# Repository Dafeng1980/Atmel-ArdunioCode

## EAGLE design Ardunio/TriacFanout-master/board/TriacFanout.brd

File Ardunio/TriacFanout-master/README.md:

Triac Fanout board for daisy-chainable 8x triac (lightbulb) outputs and Arduino library. So far tested for 8 channels.

[Video](http://instagram.com/p/sIGZ_VrQKr/?modal=true)

Written by Sean McIntyre.
MIT license, all text above must be included in any redistribution

Place the TriacFanout library folder in your <arduinosketchfolder>/libraries/ folder. You may need to create the libraries subfolder if its your first library. Restart the IDE

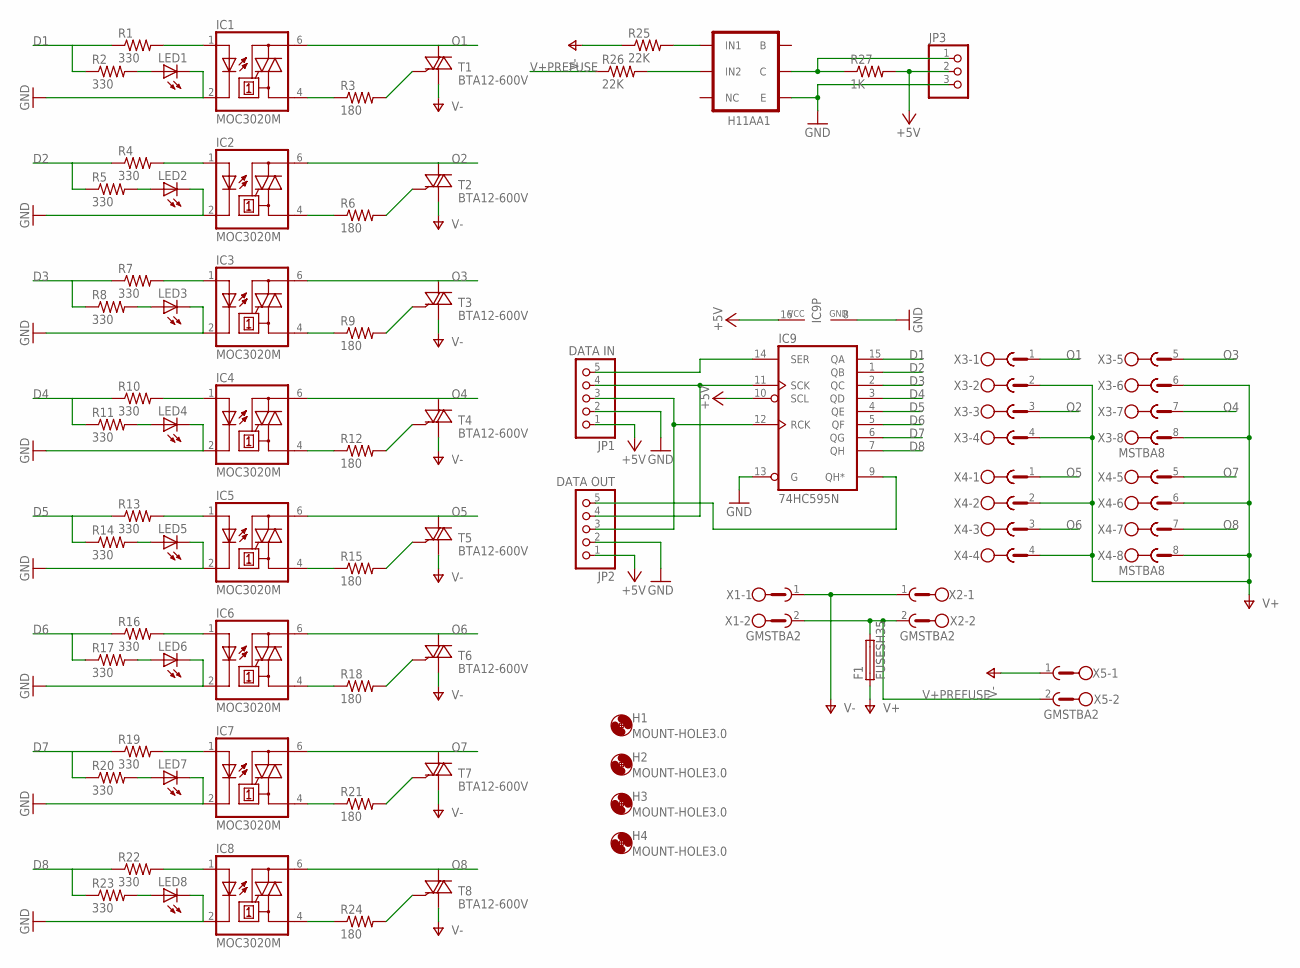
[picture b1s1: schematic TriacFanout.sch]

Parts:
F1: FUSESH35; SH25
H1, H2, H3, H4: MOUNT-HOLE3.0; 3,0
IC1, IC2, IC3, IC4, IC5, IC6, IC7, IC8: MOC3020M; DIL06
IC9: 74HC595N; DIL16
JP1: DATA IN; 1X05
JP2: DATA OUT; 1X05
JP3: PINHD-1X3; 1X03
LED1, LED2, LED3, LED4, LED5, LED6, LED7, LED8: LED5MM
R1, R2, R4, R5, R7, R8, R10, R11, R13, R14, R16, R17, R19, R20, R22, R23: 330; 0207/10
R3, R6, R9, R12, R15, R18, R21, R24: 180; 0207/10
R25, R26: 22K; 0411/12
R27: 1K; 0207/10
T1, T2, T3, T4, T5, T6, T7, T8: BTA12-600V; TO220V
U$1: H11AA1; DIL06
X1, X2, X5: GMSTBA2
X3, X4: MSTBA8

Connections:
+5V: IC9.10 (SCL), IC9.16 (VCC), JP1.1, JP2.1, JP3.2, R27.2
CLOCK: IC9.11 (SCK), JP1.4, JP2.4
D1: IC9.15 (QA), R1.1, R2.1
D2: IC9.1 (QB), R4.1, R5.1
D3: IC9.2 (QC), R7.1, R8.1
D4: IC9.3 (QD), R10.1, R11.1
D5: IC9.4 (QE), R13.1, R14.1
D6: IC9.5 (QF), R16.1, R17.1
D7: IC9.6 (QG), R19.1, R20.1
D8: IC9.7 (QH), R22.1, R23.1
DATA: IC9.14 (SER), JP1.5
GND: IC1.2 (C), IC2.2 (C), IC3.2 (C), IC4.2 (C), IC5.2 (C), IC6.2 (C), IC7.2 (C), IC8.2 (C), IC9.8 (GND), IC9.13 (G), JP1.2, JP2.2, JP3.3, LED1.K (C), LED2.K (C), LED3.K (C), LED4.K (C), LED5.K (C), LED6.K (C), LED7.K (C), LED8.K (C), U$1.4 (E)
LATCH: IC9.12 (RCK), JP1.3, JP2.3
unnamed: IC2.1 (A), R4.2
unnamed: LED2.A, R5.2
unnamed: IC2.4 (A1), R6.1
unnamed: R6.2, T2.3 (G)
unnamed: IC3.1 (A), R7.2
unnamed: LED3.A, R8.2
unnamed: IC3.4 (A1), R9.1
unnamed: R9.2, T3.3 (G)
unnamed: IC1.4 (A1), R3.1
unnamed: IC1.1 (A), R1.2
unnamed: R3.2, T1.3 (G)
unnamed: LED1.A, R2.2
unnamed: IC4.1 (A), R10.2
unnamed: LED4.A, R11.2
unnamed: IC4.4 (A1), R12.1
unnamed: R12.2, T4.3 (G)
unnamed: IC5.1 (A), R13.2
unnamed: LED5.A, R14.2
unnamed: IC5.4 (A1), R15.1
unnamed: R15.2, T5.3 (G)
unnamed: IC6.1 (A), R16.2
unnamed: LED6.A, R17.2
unnamed: IC6.4 (A1), R18.1
unnamed: R18.2, T6.3 (G)
unnamed: IC7.1 (A), R19.2
unnamed: LED7.A, R20.2
unnamed: IC7.4 (A1), R21.1
unnamed: R21.2, T7.3 (G)
unnamed: IC8.1 (A), R22.2
unnamed: LED8.A, R23.2
unnamed: IC8.4 (A1), R24.1
unnamed: R24.2, T8.3 (G)
unnamed: R25.2, U$1.1 (IN1)
unnamed: R26.2, U$1.2 (IN2)
O1: IC1.6 (A2), T1.2 (A2), X3.1
O2: IC2.6 (A2), T2.2 (A2), X3.3
O3: IC3.6 (A2), T3.2 (A2), X3.5
O4: IC4.6 (A2), T4.2 (A2), X3.7
O5: IC5.6 (A2), T5.2 (A2), X4.1
O6: IC6.6 (A2), T6.2 (A2), X4.3
O7: IC7.6 (A2), T7.2 (A2), X4.5
O8: IC8.6 (A2), T8.2 (A2), X4.7
OVERFLOW: IC9.9 (QH*), JP2.5
V+: F1.1, X3.2, X3.4, X3.6, X3.8, X4.2, X4.4, X4.6, X4.8
V+PREFUSE: F1.2, R26.1, X1.2, X2.2, X5.2
V-: R25.1, T1.1 (A1), T2.1 (A1), T3.1 (A1), T4.1 (A1), T5.1 (A1), T6.1 (A1), T7.1 (A1), T8.1 (A1), X1.1, X2.1, X5.1
ZEROCROSS: JP3.1, R27.1, U$1.5 (C)

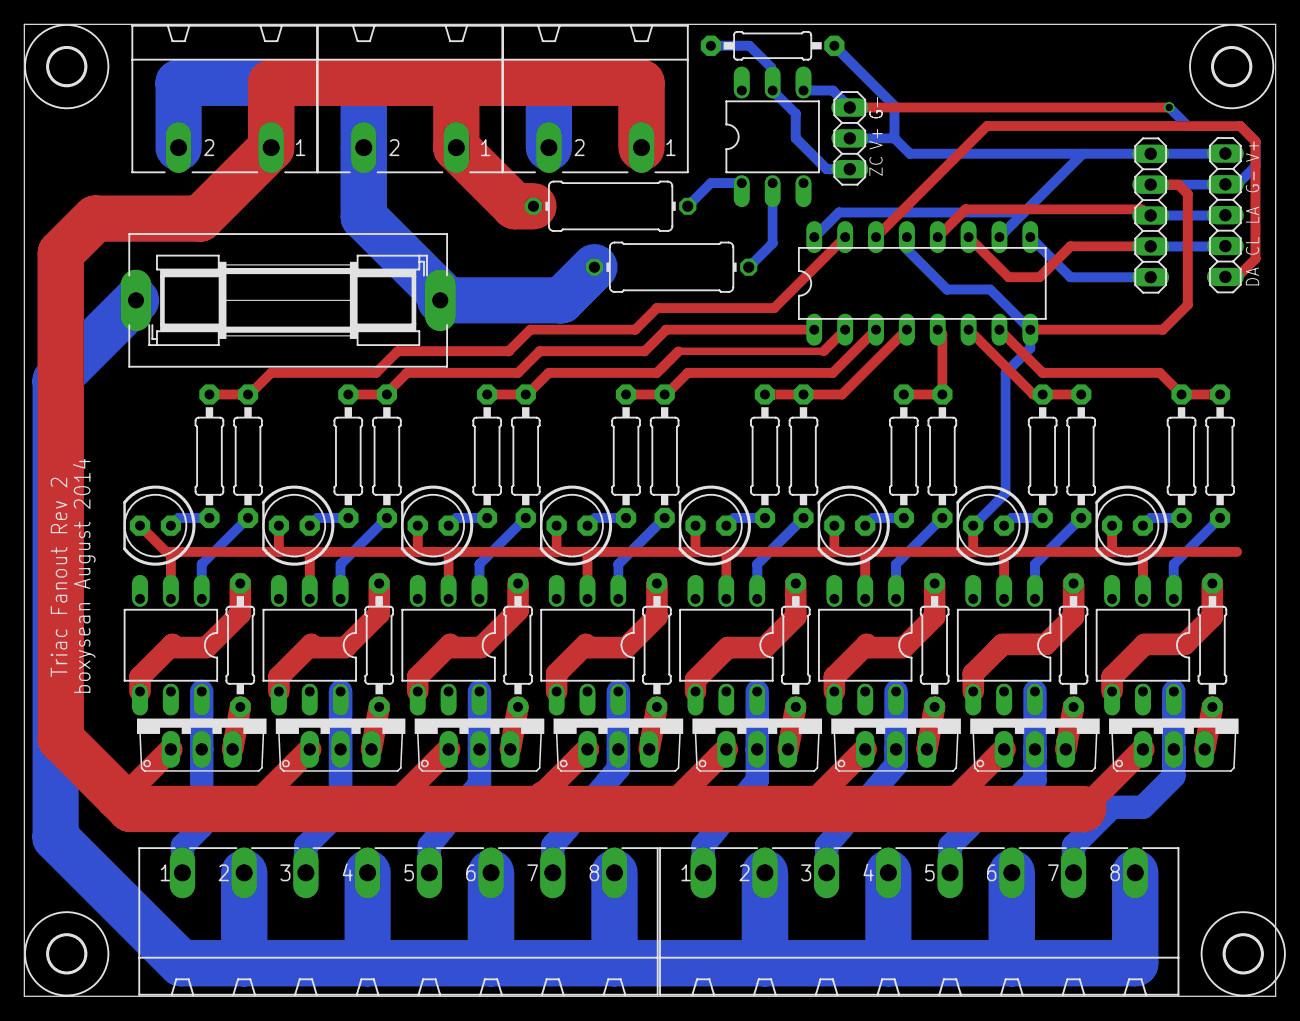
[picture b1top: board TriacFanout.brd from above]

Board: 2 copper layers, 103.0 x 80.0 mm, 66 parts (0 on the bottom side), 60 nets.

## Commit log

2019-09-09 firstUp
